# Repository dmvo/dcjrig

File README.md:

# DCJ11 test rig

**A KiCad project designed from scratch with AI assistance.**
The human gives instructions and reviews the AI's work.
This covers the circuit, custom parts, models and docs.
An autorouter lays the tracks.

[AGENTS.md](AGENTS.md) holds our working rules. Copy and adapt them for
your projects.

The rig checks DEC DCJ11-AE CPUs through their built-in ODT console.
It uses a 4 MHz crystal, a DC319A DLART and two ZIF sockets.
The [GAL source and programming file](logic/gal/README.md) are included.

**ODT works on hardware.** CPU register writes read back correctly in the
[first console check](docs/assembly.md). Five DCJ11 CPUs then passed the
[ODT test suite](tests/odt/README.md). It checks registers and the console
bus path, not every CPU function.

[Open in KiCad 10](kicad/rig/rig.kicad_pro) ·
[Build guide](docs/build.md) ·
[PCB files](dcjrig-jlcpcb-3ac8660.zip) ·
[Sources and credits](THIRD_PARTY.md)

Inspired by Peter Schranz's
[Modular DCJ11 SBC](https://www.5volts.ch/pages/dcj11sbc/).

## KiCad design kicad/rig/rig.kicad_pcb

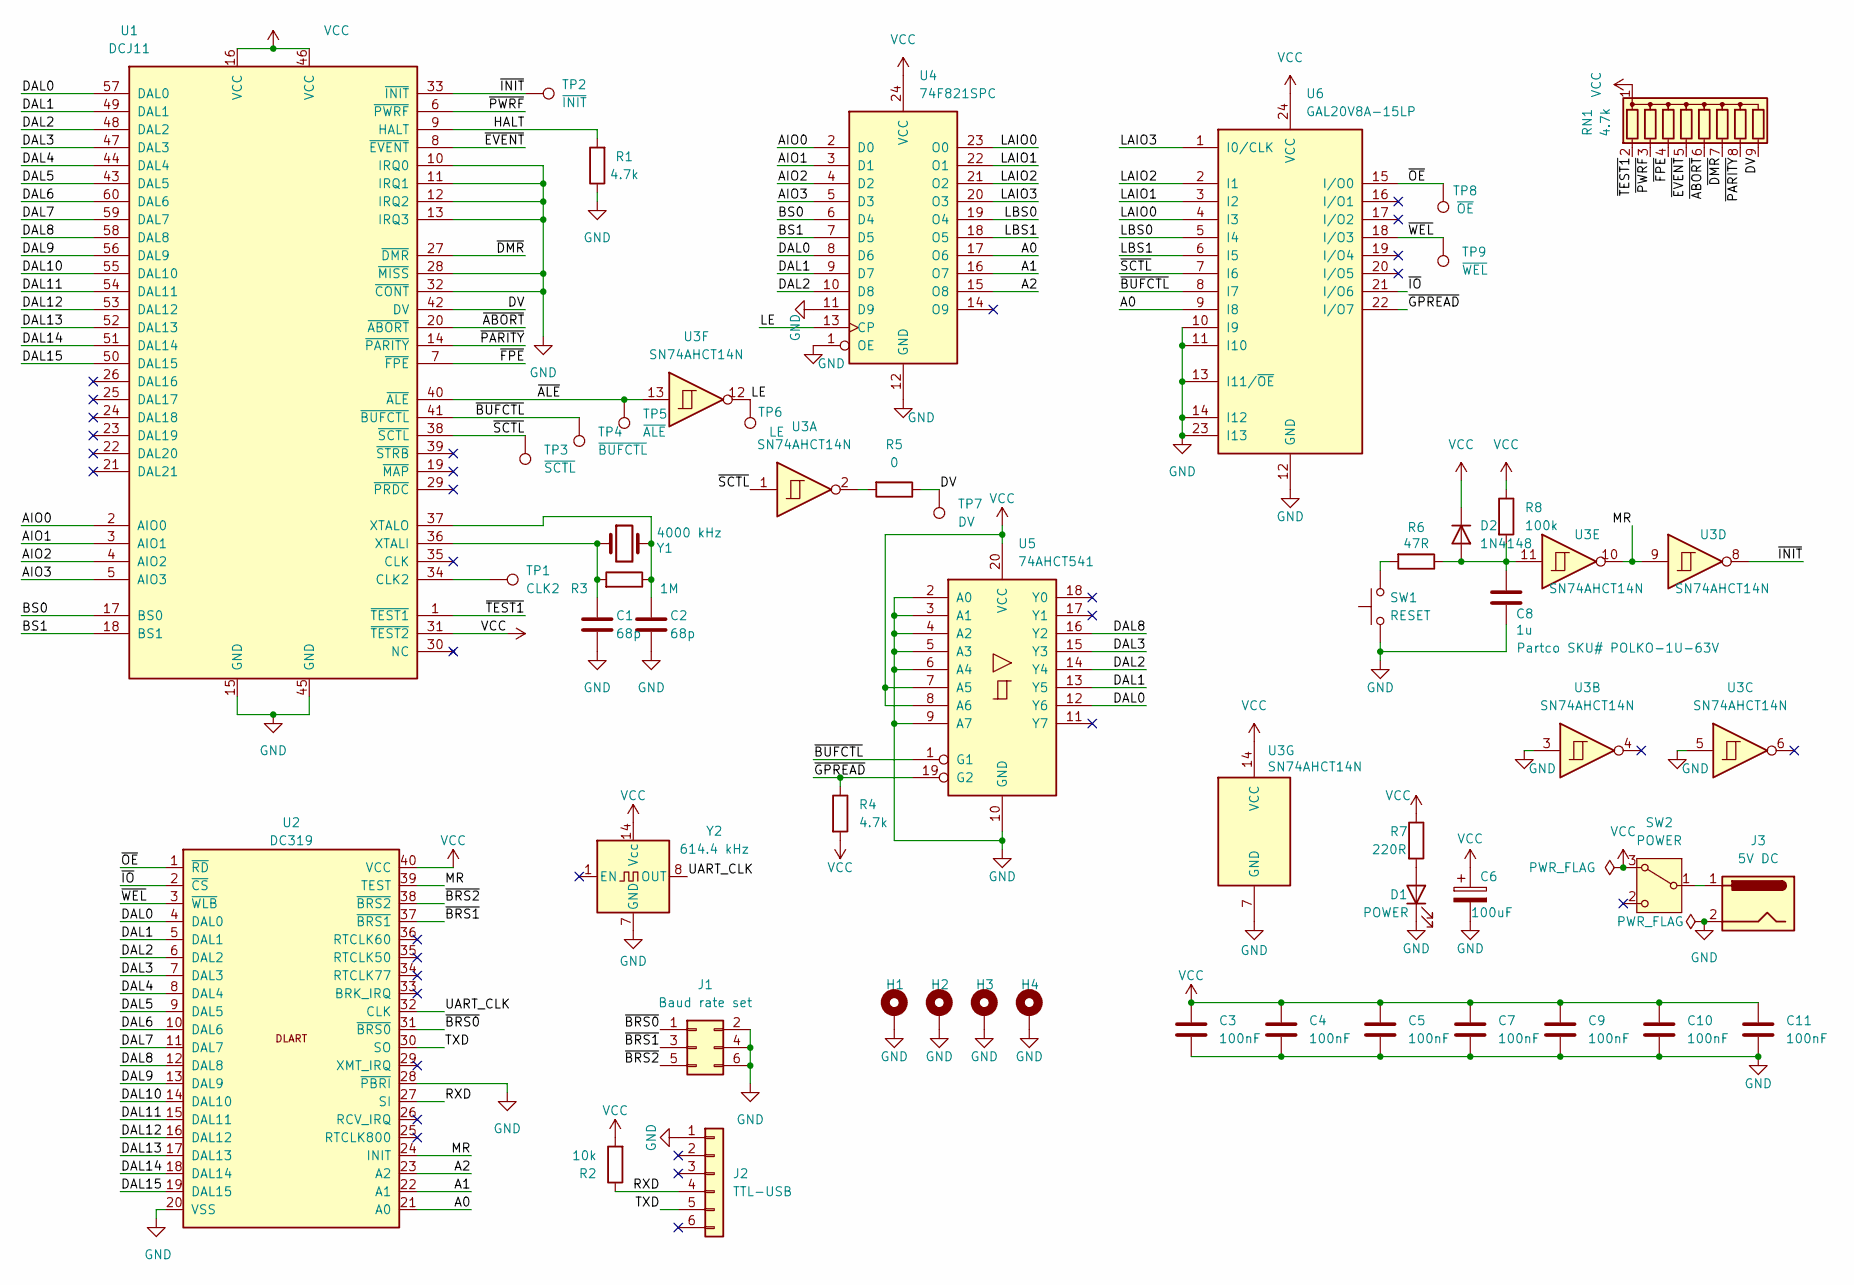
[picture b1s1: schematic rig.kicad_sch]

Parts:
C1, C2: 68p; C_Disc_D7.5mm_W4.4mm_P5.00mm
C3, C4, C5, C7, C9, C10, C11: 100nF; C_Disc_D4.7mm_W2.5mm_P5.00mm
C6: 100uF; CP_Radial_D5.0mm_P2.00mm
C8: 1u; C_Rect_L7.2mm_W5.5mm_P5.00mm_FKS2_FKP2_MKS2_MKP2; Partco Partco SKU# POLKO-1U-63V
D1: POWER; LED_D5.0mm
D2: 1N4148; D_DO-35_SOD27_P7.62mm_Horizontal
H1, H2, H3, H4: MountingHole_Pad; MountingHole_3.2mm_M3_DIN965_Pad
J1: Baud rate set; PinHeader_2x03_P2.54mm_Vertical
J2: TTL-USB; PinHeader_1x06_P2.54mm_Vertical
J3: 5V DC; BarrelJack_CUI_PJ-063AH_Horizontal
R1, R4: 4.7k; R_Axial_DIN0207_L6.3mm_D2.5mm_P10.16mm_Horizontal
R2: 10k; R_Axial_DIN0207_L6.3mm_D2.5mm_P10.16mm_Horizontal
R3: 1M; R_Axial_DIN0207_L6.3mm_D2.5mm_P10.16mm_Horizontal
R5: 0; R_Axial_DIN0207_L6.3mm_D2.5mm_P10.16mm_Horizontal
R6: 47R; R_Axial_DIN0207_L6.3mm_D2.5mm_P10.16mm_Horizontal
R7: 220R; R_Axial_DIN0414_L11.9mm_D4.5mm_P7.62mm_Vertical
R8: 100k; R_Axial_DIN0207_L6.3mm_D2.5mm_P10.16mm_Horizontal
RN1: 4.7k; R_Array_SIP9
SW1: RESET; SW_PUSH_6mm
SW2: POWER; SW_Slide-03_Wuerth-WS-SLTV_10x2.5x6.4_P2.54mm
TP1: CLK2; PinHeader_1x01_P2.54mm_Vertical
TP2: ~{INIT}; PinHeader_1x01_P2.54mm_Vertical
TP3: ~{SCTL}; PinHeader_1x01_P2.54mm_Vertical
TP4: ~{BUFCTL}; PinHeader_1x01_P2.54mm_Vertical
TP5: ~{ALE}; PinHeader_1x01_P2.54mm_Vertical
TP6: LE; PinHeader_1x01_P2.54mm_Vertical
TP7: DV; PinHeader_1x01_P2.54mm_Vertical
TP8: ~{OE}; PinHeader_1x01_P2.54mm_Vertical
TP9: ~{WEL}; PinHeader_1x01_P2.54mm_Vertical
U1: DCJ11; DCJ11_DIP60_2xTextool_264-4493_ZIF
U2: DC319; DIP-40_W15.24mm_Socket_LongPads
U3: SN74AHCT14N; DIP-14_W7.62mm_Socket_LongPads
U4: 74F821SPC; DIP-24_W7.62mm_Socket_LongPads
U5: 74AHCT541; DIP-20_W7.62mm_Socket_LongPads
U6: GAL20V8A-15LP; DIP-24_W7.62mm_Socket_LongPads
Y1: 4000 kHz; Crystal_HC49S_Vertical
Y2: 614.4 kHz; Oscillator_DIP-14

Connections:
/A0: U2.21 (A0), U4.17 (O6), U6.9 (I8)
/A1: U2.22 (A1), U4.16 (O7)
/A2: U2.23 (A2), U4.15 (O8)
/AIO0: U1.2 (AIO0), U4.2 (D0)
/AIO1: U1.3 (AIO1), U4.3 (D1)
/AIO2: U1.4 (AIO2), U4.4 (D2)
/AIO3: U1.5 (AIO3), U4.5 (D3)
/BS0: U1.17 (BS0), U4.6 (D4)
/BS1: U1.18 (BS1), U4.7 (D5)
/DAL0: U1.57 (DAL0), U2.4 (DAL0), U4.8 (D6), U5.12 (Y6)
/DAL1: U1.49 (DAL1), U2.5 (DAL1), U4.9 (D7), U5.13 (Y5)
/DAL2: U1.48 (DAL2), U2.6 (DAL2), U4.10 (D8), U5.14 (Y4)
/DAL3: U1.47 (DAL3), U2.7 (DAL3), U5.15 (Y3)
/DAL4: U1.44 (DAL4), U2.8 (DAL4)
/DAL5: U1.43 (DAL5), U2.9 (DAL5)
/DAL6: U1.60 (DAL6), U2.10 (DAL6)
/DAL7: U1.59 (DAL7), U2.11 (DAL7)
/DAL8: U1.58 (DAL8), U2.12 (DAL8), U5.16 (Y2)
/DAL9: U1.56 (DAL9), U2.13 (DAL9)
/DAL10: U1.55 (DAL10), U2.14 (DAL10)
/DAL11: U1.54 (DAL11), U2.15 (DAL11)
/DAL12: U1.53 (DAL12), U2.16 (DAL12)
/DAL13: U1.52 (DAL13), U2.17 (DAL13)
/DAL14: U1.51 (DAL14), U2.18 (DAL14)
/DAL15: U1.50 (DAL15), U2.19 (DAL15)
/DV: R5.1, RN1.9 (R8), TP7.1 (1_1), U1.42 (DV)
/HALT: R1.2, U1.9 (HALT)
/LAIO0: U4.23 (O0), U6.4 (I3)
/LAIO1: U4.22 (O1), U6.3 (I2)
/LAIO2: U4.21 (O2), U6.2 (I1)
/LAIO3: U4.20 (O3), U6.1 (I0/CLK)
/LBS0: U4.19 (O4), U6.5 (I4)
/LBS1: U4.18 (O5), U6.6 (I5)
/LE: TP6.1 (1_1), U3.12, U4.13 (CP)
/MR: U2.24 (INIT), U2.39 (TEST), U3.9, U3.10
/RXD: J2.4, R2.1, U2.27 (SI)
/TXD: J2.5, U2.30 (SO)
/UART_CLK: U2.32 (CLK), Y2.8 (OUT)
/~ABORT: RN1.6 (R5), U1.20 (~ABORT)
/~ALE: TP5.1 (1_1), U1.40 (~ALE), U3.13
/~BRS0: J1.1, U2.31 (~BRS0)
/~BRS1: J1.3, U2.37 (~BRS1)
/~BRS2: J1.5, U2.38 (~BRS2)
/~BUFCTL: TP4.1 (1_1), U1.41 (~BUFCTL), U5.1 (G1), U6.8 (I7)
/~DMR: RN1.7 (R6), U1.27 (~DMR)
/~EVENT: RN1.5 (R4), U1.8 (~EVENT)
/~FPE: RN1.4 (R3), U1.7 (~FPE)
/~GPREAD: R4.1, U5.19 (G2), U6.22 (I/O7)
/~INIT: TP2.1 (1_1), U1.33 (~INIT), U3.8
/~IO: U2.2 (~CS), U6.21 (I/O6)
/~OE: TP8.1 (1_1), U2.1 (~RD), U6.15 (I/O0)
/~PARITY: RN1.8 (R7), U1.14 (~PARITY)
/~PWRF: RN1.3 (R2), U1.6 (~PWRF)
/~SCTL: TP3.1 (1_1), U1.38 (~SCTL), U3.1, U6.7 (I6)
/~TEST1: RN1.2 (R1), U1.1 (~TEST1)
/~WEL: TP9.1 (1_1), U2.3 (~WLB), U6.18 (I/O3)
GND: C1.2, C2.2, C3.2, C4.2, C5.2, C6.2, C7.2, C8.2, C9.2, C10.2, C11.2, D1.1 (K), H1.1 (1_1), H2.1 (1_1), H3.1 (1_1), H4.1 (1_1), J1.2, J1.4, J1.6, J2.1, J3.2, R1.1, SW1.1, U1.10 (IRQ0), U1.11 (IRQ1), U1.12 (IRQ2), U1.13 (IRQ3), U1.15 (GND), U1.28 (~MISS), U1.32 (~CONT), U1.45 (GND), U2.20 (VSS), U2.28 (~PBRI), U3.3, U3.5, U3.7 (GND), U4.1 (OE), U4.11 (D9), U4.12 (GND), U5.2 (A0), U5.3 (A1), U5.4 (A2), U5.5 (A3), U5.6 (A4), U5.9 (A7), U5.10 (GND), U6.10 (I9), U6.11 (I10), U6.12 (GND), U6.13 (I11/~OE), U6.14 (I12), U6.23 (I13), Y2.7 (GND)
unnamed: D1.2 (A), R7.2
unnamed: C8.1, D2.2 (A), R6.1, R8.2, U3.11
unnamed: R5.2, U3.2
unnamed: R6.2, SW1.2
unnamed: J3.1, SW2.1 (B)
unnamed: TP1.1 (1_1), U1.34 (CLK2)
unnamed: C1.1, R3.2, U1.36 (XTALI), Y1.1
unnamed: C2.1, R3.1, U1.37 (XTALO), Y1.2
VCC: C3.1, C4.1, C5.1, C6.1, C7.1, C9.1, C10.1, C11.1, D2.1 (K), R2.2, R4.2, R7.1, R8.1, RN1.1 (common), SW2.3 (A), U1.16 (VCC), U1.31 (~TEST2), U1.46 (VCC), U2.40 (VCC), U3.14 (VCC), U4.24 (VCC), U5.7 (A5), U5.8 (A6), U5.20 (VCC), U6.24 (VCC), Y2.14 (Vcc)

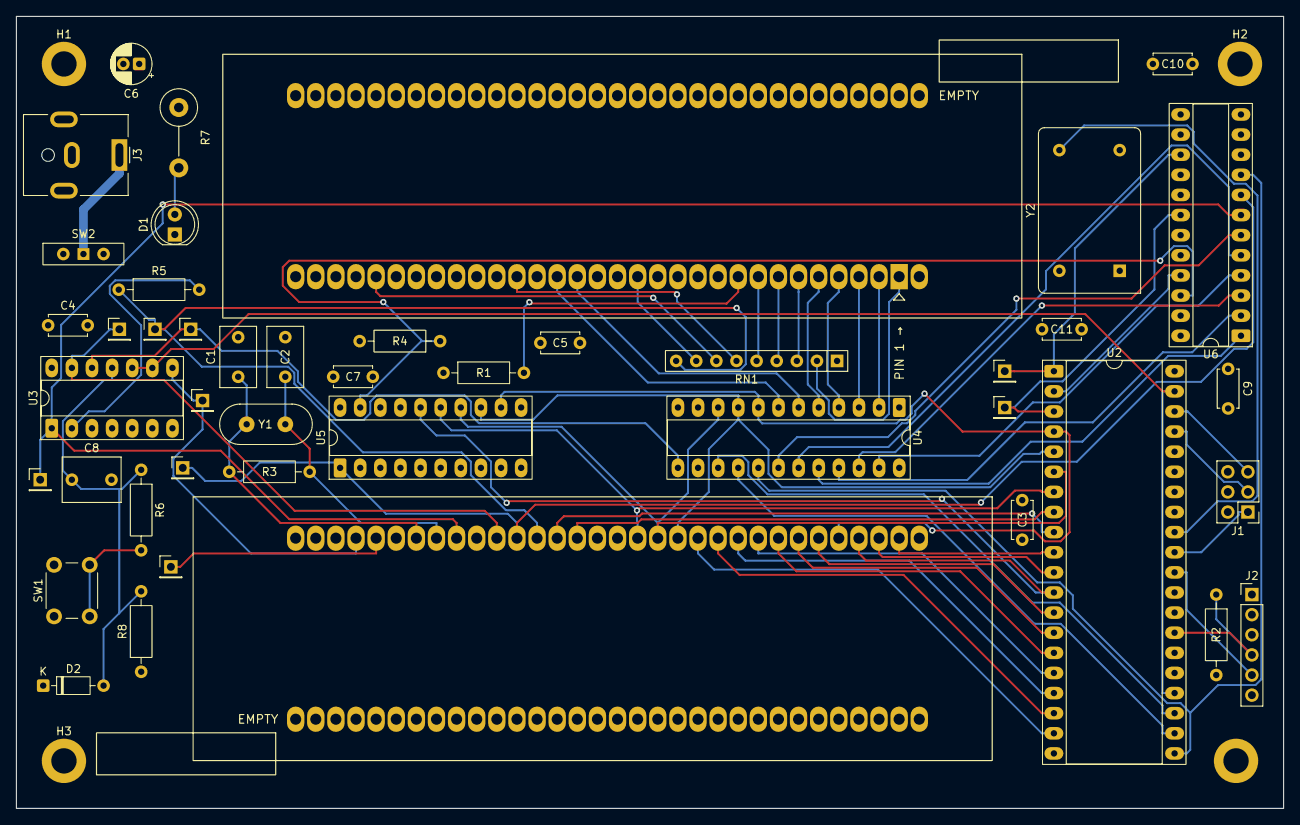
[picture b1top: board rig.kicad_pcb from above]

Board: 4 copper layers, 160.0 x 100.0 mm, 48 parts (0 on the bottom side), 66 nets.
